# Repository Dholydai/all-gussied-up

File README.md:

# all-gussied-up

MAJOR CHANGES HAVE ARRIVED!

This repository will be removed shortly. Most variants have been moved to a new one called writerz-with-an-attitude.

I designed wonderfully sleek cases for my Dvorak 2024. All of my keyboard PCBs have been reworked to fit the new cases... except the TKL

The custom Cherry MX KiCad footprint library used is posted at https://github.com/Dholydai/mx-switch-custom

Please visit https://quixotickeyboards.com for more information.

Ronald Walker

23 Jul 2024 posted the left-hand and right-hand compact files. The trio is completed!

14 Aug 2024 posted the two-hand TKL files.

23 Oct 2024 changed the firmware files for the compact trio. Better edit key layout.

22 Jan 2025 closed out all folders except the TKL variant.

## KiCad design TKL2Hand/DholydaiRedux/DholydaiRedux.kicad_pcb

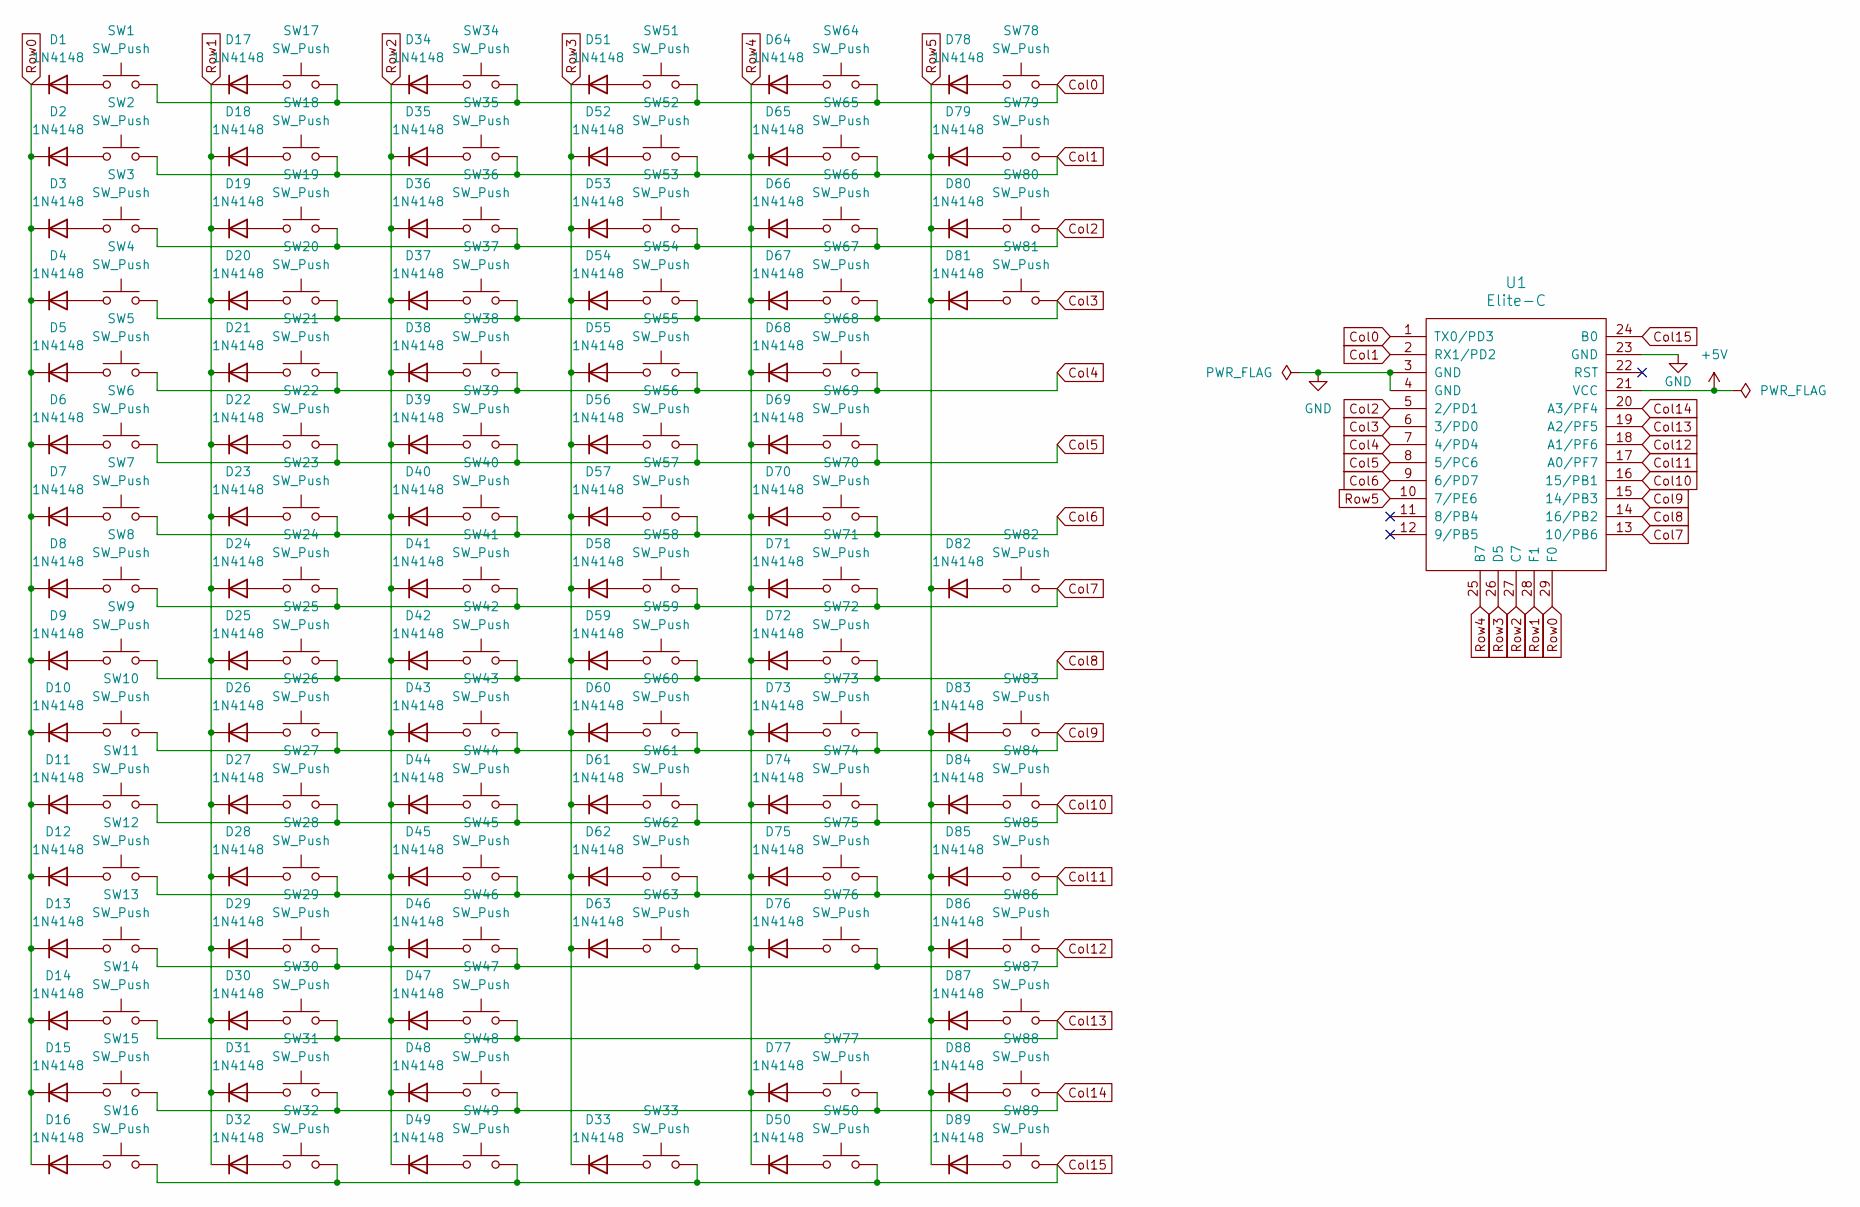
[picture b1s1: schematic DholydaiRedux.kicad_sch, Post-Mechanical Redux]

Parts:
D1, D2, D3, D4, D5, D6, D7, D8, D9, D10, D11, D12, D13, D14, D15, D16, D17, D18, D19, D20, D21, D22, D23, D24, D25, D26, D27, D28, D29, D30, D31, D32, D33, D34, D35, D36, D37, D38, D39, D40, D41, D42, D43, D44, D45, D46, D47, D48, D49, D50, D51, D52, D53, D54, D55, D56, D57, D58, D59, D60, D61, D62, D63, D64, D65, D66, D67, D68, D69, D70, D71, D72, D73, D74, D75, D76, D77, D78, D79, D80, D81, D82, D83, D84, D85, D86, D87, D88, D89: 1N4148; D_DO-35_SOD27_P7.62mm_Horizontal
SW1, SW2, SW3, SW4, SW5, SW6, SW7, SW8, SW9, SW10, SW11, SW12, SW13, SW14, SW15, SW16, SW18, SW19, SW20, SW21, SW22, SW23, SW24, SW25, SW26, SW27, SW28, SW29, SW31, SW32, SW33, SW35, SW36, SW37, SW38, SW39, SW40, SW41, SW42, SW43, SW44, SW45, SW46, SW48, SW49, SW50, SW52, SW53, SW54, SW55, SW56, SW58, SW59, SW60, SW61, SW62, SW65, SW66, SW67, SW68, SW69, SW71, SW72, SW73, SW74, SW75, SW77, SW79, SW80, SW84, SW85, SW87, SW88, SW89: SW_Push; SW_Cherry_MX_1.00u_PCB
SW17, SW30, SW64, SW76: SW_Push; SW_Cherry_MX_1.50u_PCB
SW34, SW47: SW_Push; SW_Cherry_MX_1.1666u_PCB
SW51, SW63: SW_Push; SW_Cherry_MX_1.8333u_PCB
SW57: SW_Push; SW_Cherry_MX_1.3333u_PCB
SW70: SW_Push; SW_Cherry_MX_2.00u_PCB
SW78, SW81, SW83, SW86: SW_Push; SW_Cherry_MX_1.25u_PCB
SW82: SW_Push; SW_Cherry_MX_6.00u_PCB_Stagger
U1: Elite-C

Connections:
+5V: U1.21 (VCC)
Col0: SW1.2, SW17.2, SW34.2, SW51.2, SW64.2, SW78.2, U1.1 (TX0/PD3)
Col1: SW2.2, SW18.2, SW35.2, SW52.2, SW65.2, SW79.2, U1.2 (RX1/PD2)
Col2: SW3.2, SW19.2, SW36.2, SW53.2, SW66.2, SW80.2, U1.5 (2/PD1)
Col3: SW4.2, SW20.2, SW37.2, SW54.2, SW67.2, SW81.2, U1.6 (3/PD0)
Col4: SW5.2, SW21.2, SW38.2, SW55.2, SW68.2, U1.7 (4/PD4)
Col5: SW6.2, SW22.2, SW39.2, SW56.2, SW69.2, U1.8 (5/PC6)
Col6: SW7.2, SW23.2, SW40.2, SW57.2, SW70.2, U1.9 (6/PD7)
Col7: SW8.2, SW24.2, SW41.2, SW58.2, SW71.2, SW82.2, U1.13 (10/PB6)
Col8: SW9.2, SW25.2, SW42.2, SW59.2, SW72.2, U1.14 (16/PB2)
Col9: SW10.2, SW26.2, SW43.2, SW60.2, SW73.2, SW83.2, U1.15 (14/PB3)
Col10: SW11.2, SW27.2, SW44.2, SW61.2, SW74.2, SW84.2, U1.16 (15/PB1)
Col11: SW12.2, SW28.2, SW45.2, SW62.2, SW75.2, SW85.2, U1.17 (A0/PF7)
Col12: SW13.2, SW29.2, SW46.2, SW63.2, SW76.2, SW86.2, U1.18 (A1/PF6)
Col13: SW14.2, SW30.2, SW47.2, SW87.2, U1.19 (A2/PF5)
Col14: SW15.2, SW31.2, SW48.2, SW77.2, SW88.2, U1.20 (A3/PF4)
Col15: SW16.2, SW32.2, SW33.2, SW49.2, SW50.2, SW89.2, U1.24 (B0)
GND: U1.3 (GND), U1.4 (GND), U1.23 (GND)
unnamed: D1.2 (A), SW1.1
unnamed: D2.2 (A), SW2.1
unnamed: D3.2 (A), SW3.1
unnamed: D4.2 (A), SW4.1
unnamed: D5.2 (A), SW5.1
unnamed: D6.2 (A), SW6.1
unnamed: D7.2 (A), SW7.1
unnamed: D8.2 (A), SW8.1
unnamed: D9.2 (A), SW9.1
unnamed: D10.2 (A), SW10.1
unnamed: D11.2 (A), SW11.1
unnamed: D12.2 (A), SW12.1
unnamed: D13.2 (A), SW13.1
unnamed: D14.2 (A), SW14.1
unnamed: D15.2 (A), SW15.1
unnamed: D16.2 (A), SW16.1
unnamed: D17.2 (A), SW17.1
unnamed: D18.2 (A), SW18.1
unnamed: D19.2 (A), SW19.1
unnamed: D20.2 (A), SW20.1
unnamed: D21.2 (A), SW21.1
unnamed: D22.2 (A), SW22.1
unnamed: D23.2 (A), SW23.1
unnamed: D24.2 (A), SW24.1
unnamed: D25.2 (A), SW25.1
unnamed: D26.2 (A), SW26.1
unnamed: D27.2 (A), SW27.1
unnamed: D28.2 (A), SW28.1
unnamed: D29.2 (A), SW29.1
unnamed: D30.2 (A), SW30.1
unnamed: D31.2 (A), SW31.1
unnamed: D32.2 (A), SW32.1
unnamed: D33.2 (A), SW33.1
unnamed: D34.2 (A), SW34.1
unnamed: D35.2 (A), SW35.1
unnamed: D36.2 (A), SW36.1
unnamed: D37.2 (A), SW37.1
unnamed: D38.2 (A), SW38.1
unnamed: D39.2 (A), SW39.1
unnamed: D40.2 (A), SW40.1
unnamed: D41.2 (A), SW41.1
unnamed: D42.2 (A), SW42.1
unnamed: D43.2 (A), SW43.1
unnamed: D44.2 (A), SW44.1
unnamed: D45.2 (A), SW45.1
unnamed: D46.2 (A), SW46.1
unnamed: D47.2 (A), SW47.1
unnamed: D48.2 (A), SW48.1
unnamed: D49.2 (A), SW49.1
unnamed: D50.2 (A), SW50.1
unnamed: D51.2 (A), SW51.1
unnamed: D52.2 (A), SW52.1
unnamed: D53.2 (A), SW53.1
unnamed: D54.2 (A), SW54.1
unnamed: D55.2 (A), SW55.1
unnamed: D56.2 (A), SW56.1
unnamed: D57.2 (A), SW57.1
unnamed: D58.2 (A), SW58.1
unnamed: D59.2 (A), SW59.1
unnamed: D60.2 (A), SW60.1
unnamed: D61.2 (A), SW61.1
unnamed: D62.2 (A), SW62.1
unnamed: D63.2 (A), SW63.1
unnamed: D64.2 (A), SW64.1
unnamed: D65.2 (A), SW65.1
unnamed: D66.2 (A), SW66.1
unnamed: D67.2 (A), SW67.1
unnamed: D68.2 (A), SW68.1
unnamed: D69.2 (A), SW69.1
unnamed: D70.2 (A), SW70.1
unnamed: D71.2 (A), SW71.1
unnamed: D72.2 (A), SW72.1
unnamed: D73.2 (A), SW73.1
unnamed: D74.2 (A), SW74.1
unnamed: D75.2 (A), SW75.1
unnamed: D76.2 (A), SW76.1
unnamed: D77.2 (A), SW77.1
unnamed: D78.2 (A), SW78.1
unnamed: D79.2 (A), SW79.1
unnamed: D80.2 (A), SW80.1
unnamed: D81.2 (A), SW81.1
unnamed: D82.2 (A), SW82.1
unnamed: D83.2 (A), SW83.1
unnamed: D84.2 (A), SW84.1
unnamed: D85.2 (A), SW85.1
unnamed: D86.2 (A), SW86.1
unnamed: D87.2 (A), SW87.1
unnamed: D88.2 (A), SW88.1
unnamed: D89.2 (A), SW89.1
Row0: D1.1 (K), D2.1 (K), D3.1 (K), D4.1 (K), D5.1 (K), D6.1 (K), D7.1 (K), D8.1 (K), D9.1 (K), D10.1 (K), D11.1 (K), D12.1 (K), D13.1 (K), D14.1 (K), D15.1 (K), D16.1 (K), U1.29 (F0)
Row1: D17.1 (K), D18.1 (K), D19.1 (K), D20.1 (K), D21.1 (K), D22.1 (K), D23.1 (K), D24.1 (K), D25.1 (K), D26.1 (K), D27.1 (K), D28.1 (K), D29.1 (K), D30.1 (K), D31.1 (K), D32.1 (K), U1.28 (F1)
Row2: D34.1 (K), D35.1 (K), D36.1 (K), D37.1 (K), D38.1 (K), D39.1 (K), D40.1 (K), D41.1 (K), D42.1 (K), D43.1 (K), D44.1 (K), D45.1 (K), D46.1 (K), D47.1 (K), D48.1 (K), D49.1 (K), U1.27 (C7)
Row3: D33.1 (K), D51.1 (K), D52.1 (K), D53.1 (K), D54.1 (K), D55.1 (K), D56.1 (K), D57.1 (K), D58.1 (K), D59.1 (K), D60.1 (K), D61.1 (K), D62.1 (K), D63.1 (K), U1.26 (D5)
Row4: D50.1 (K), D64.1 (K), D65.1 (K), D66.1 (K), D67.1 (K), D68.1 (K), D69.1 (K), D70.1 (K), D71.1 (K), D72.1 (K), D73.1 (K), D74.1 (K), D75.1 (K), D76.1 (K), D77.1 (K), U1.25 (B7)
Row5: D78.1 (K), D79.1 (K), D80.1 (K), D81.1 (K), D82.1 (K), D83.1 (K), D84.1 (K), D85.1 (K), D86.1 (K), D87.1 (K), D88.1 (K), D89.1 (K), U1.10 (7/PE6)

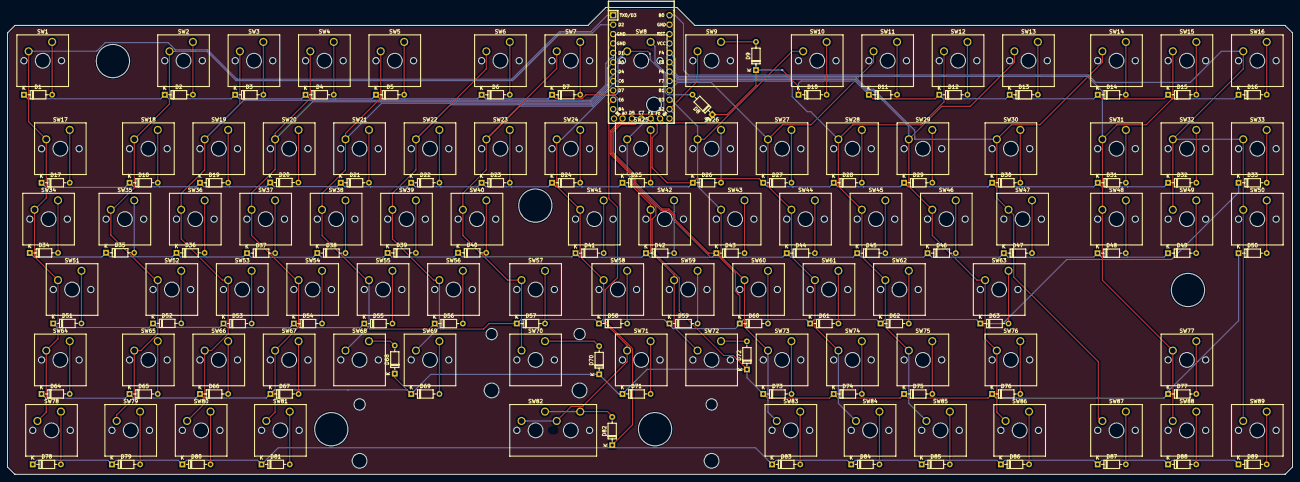
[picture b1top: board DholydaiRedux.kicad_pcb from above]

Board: 2 copper layers, 347.7 x 126.3 mm, 179 parts (0 on the bottom side), 112 nets.

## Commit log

2024-06-23 Create holder
2024-06-23 3D Printing Files
2024-06-23 Files for 3D printing the case
2024-06-23 Files from the PCB design
2024-06-23 Files for QMK firmware installation
2024-06-23 Compact Post-Mechanical keyboard
2024-06-29 Two-Hand Post-Mechanical compact keyboard
2024-07-10 Create Temp
2024-07-10 Create temp2
2024-07-10 Create temp3
2024-07-10 Improved tolerances on bottom files. Renamed all files.
2024-07-10 Renamed files with improved tolerances.
2024-07-10 Improved 3D print files
2024-07-10 Files for 3D printed keyboard cases
2024-07-10 Renamed files with improved toleances
2024-07-10 Create Temp4
2024-07-10 Renamed files with improved tolerances
2024-07-10 Create temp5
2024-07-10 Two-hand compact human factored keyboard
2024-07-10 Firmware development files
2024-07-10 Create temp6
2024-07-10 Create temp7
2024-07-10 Two-hand compact keyboard
2024-07-23 Create exit
2024-07-23 OpenSCAD files from the PCB design
2024-07-23 Files from the keyboard case design
2024-07-23 Create filler
2024-07-23 Files to make the keyboard case
2024-07-23 CompactLeftHand
2024-07-23 Left-Hand Compact Keyboard
2024-07-23 Create aoe
2024-07-23 Create oeu
2024-07-23 Files for QMK firmware install
2024-07-23 Create aoeui
2024-07-23 Files to 3D print a case
2024-07-23 Files to make a keyboard case
2024-07-23 Create qjk
2024-07-23 Delete CompLeft-Hand/LeftHndCompCase/stl/qjk
    Files for 3D printing the case
2024-07-23 Create dhtn
2024-07-23 Create aoeu
2024-07-23 Create CompRight-Hand
2024-07-23 Create eui
2024-07-23 Create dht
2024-07-23 Create bmw
2024-07-23 Create fgc
2024-07-23 Create htn
2024-07-23 Right-Hand Compact Keyboard
2024-07-26 Create pyiu
2024-08-15 Files to print the keyboard case
2024-08-15 Create jkx
2024-08-15 Create eoa
2024-08-15 Create uid
2024-08-15 Create ekx
2024-08-15 Create mwv
2024-08-15 Two-Hand TKL Keyboard
2024-10-24 New QMK firmware files
2025-01-22 Removed all variants except for the TKL
